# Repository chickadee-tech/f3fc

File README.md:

# Chickadee Tech F3FC #
This an STM32F3-based flight control Polystack board for multirotors designed by Chickadee Tech. It features an STM32F303VCT6 microcontroller and an MPU-6000 accelerometer/gyroscope. It runs a modified version of [Betaflight]() available [here](github.com/chickadee-tech/betaflight) with the CKD_F3FC target.

## Documentation ##
See the [wiki](https://github.com/chickadee-tech/f3fc/wiki) for documentation.

## Polystack ##
This **control** board is part of the Polystack platform for modular microcontrol systems. More information on the platform can be found at [polystack.org](http://polystack.org).

## Support ##
If you need support with a board you own or have development questions please email support@chickadee.tech or check chickadee.tech/support for other ways to get support.

## Support ##
If you need support with a board you own or have development questions please email support@chickadee.tech or check [chickadee.tech/support](https://chickadee.tech/support) for other ways to get support.

## Contributing ##
Please note that this project is released with a [Contributor Code of Conduct](CODE_OF_CONDUCT.md). By participating in this project you agree to abide by its terms.

### Setup ###
Components and footprints for PCB parts are not included in this repository. Instead, checkout the [chickadee-tech/kicad-libs](https://github.com/chickadee-tech/kicad-libs) repository in the same directory that this repository is checked out in. All part definitions should be relative so that they will load correctly.

### Pull requests ###
For fixes please submit a pull request to the original repository. After the pull request is merged, check the [Chickadee Tech Active Contributor Discount (ACD)](https://chickadee.tech/active-contributor) to see if you are eligible for a discount code to use on your next purchase.

### Derivatives ###
If developing your own version of the F3FC board please remove all Chickadee Tech trademarks and follow the [CC-BY license](LICENSE). While not required, please consider open sourcing your modifications so others can learn from your improvements. If you do email support@chickadee.tech and we may choose to add your project to the ACD.

You may also license the Polystack logo for free by emailing support@chickadee.tech. We'll ask for your gerbers to ensure the design complies with specifications laid out [here](https://github.com/chickadee-tech/polystack/wiki) and provide written permission to use the trademark after compliance has been demonstrated.

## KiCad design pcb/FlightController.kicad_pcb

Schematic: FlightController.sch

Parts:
C1: 2.2nF; C_0603_HandSoldering
C2, C3, C7, C8, C9, C10, C13: 0.1uF; C_0603_HandSoldering
C5: 10nF; C_0603_HandSoldering
C14: 2.2uF; C_0603_HandSoldering
D1: Green; LED-0603
D2: Yellow; LED-0603
D3: Red; LED-0603
P2: USB_OTG; Mini-USB-B
P3: CONN_02X04; Pin_Header_Angled_2x04
P4: CKD_SANDWICH; DF40-3-4mm-80pin-Receptacle
P10: SWDIO; Measurement_Point_Round-SMD-Pad_Small
P11: SWCLK; Measurement_Point_Round-SMD-Pad_Small
R1, R2, R3: 1k; R_0603_HandSoldering
R4, R11: 4.7k; R_0603_HandSoldering
R5: 10k+; R_0603_HandSoldering
R6: 1.5k; R_0603_HandSoldering
U1: MPU-6000; QFN-24-1EP_4x4mm_Pitch0.5mm
U2: STM32F303x{B,C}; LQFP-100_14x14mm_Pitch0.5mm
X1: 8MHZ; CSTCE_G-CSTCE_G_Z

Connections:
+5V: P4.19 (5V_0.3A), P4.20 (5V_0.3A), P4.21 (5V_0.3A), P4.22 (5V_0.3A), P4.23 (5V_0.3A), P4.24 (5V_0.3A); also elsewhere on the board
+5VA: P2.1 (VCC); also elsewhere on the board
+BATT: P4.18 (+BATT), U2.15 (PC0/ADC12_IN6); also elsewhere on the board
/ADC1: P4.49 (ADC1), U2.16 (PC1/ADC12_IN7)
/ADC2: P4.50 (ADC2), U2.17 (PC2/ADC12_IN8)
/GPIO2_4: P4.7 (GPIO3), U2.3 (PE4/TIM3_CH3)
/GPIO3_3: P4.8 (GPIO4), U2.2 (PE3/TIM3_CH2)
/GPIO4_2: P4.9 (xi2c_SDA), U2.1 (PE2/TIM3_CH1)
/LED0: R3.1, U2.7 (PC13)
/LED1: R2.1, U2.8 (PC14/OSC32_IN)
/LED2: R1.1, U2.9 (PC15/OSC32_OUT)
/MPU_INT: U1.12, U2.35 (PB0)
/PA14_SWCLK: P4.6 (GPIO2), P11.1, U2.76 (PA14/TIM8_CH2)
/PB7: P4.10 (xi2c_SCL), U2.93 (PB7/I2C1_SDA)
/Power/CURRENT: U2.18 (PC3/ADC12_IN9); also elsewhere on the board
/Reset/BOOT0: P4.65 (SPI4_NSS), R5.2, U2.94 (BOOT0); also elsewhere on the board
/Reset/RESET: C13.1, P4.66 (SPI4_SCK), U2.14 (NRST); also elsewhere on the board
/SPI1_MISO: U1.9, U2.31 (PA6/SPI1_MISO)
/SPI1_MOSI: U1.24, U2.32 (PA7/SPI1_MOSI)
/SPI1_NSS: U1.8, U2.29 (PA4/SPI1_NSS)
/SPI1_SCK: U1.23, U2.30 (PA5/SPI1_SCK)
/SPI2_MISO: P4.79 (SPI1_MISO), U2.53 (PB14/SPI2_MISO)
/SPI2_MOSI: P4.80 (SPI1_MOSI), U2.54 (PB15/SPI2_MOSI)
/SPI2_NSS: P4.77 (SPI1_NSS), U2.51 (PB12/SPI2_NSS)
/SPI2_SCK: P4.78 (SPI1_SCK), U2.52 (PB13/SPI2_SCK)
/SPI3_MISO: P4.75 (SPI2_MISO), U2.90 (PB4/SPI3_MISO)
/SPI3_MOSI: P4.76 (SPI2_MOSI), U2.91 (PB5/SPI3_MOSI)
/SPI3_NSS: P4.73 (SPI2_NSS), U2.77 (PA15/SPI3_NSS)
/SPI3_SCK: P4.74 (SPI2_SCK), U2.89 (PB3/SPI3_SCK)
/SWDIO_13: P4.5 (GPIO1), P10.1, U2.72 (PA13)
/TIM1_CH1: P3.2, U2.40 (PE9/TIM1_CH1)
/TIM1_CH2: P3.4, U2.42 (PE11/TIM1_CH2)
/TIM1_CH3: P3.6, U2.44 (PE13/TIM1_CH3)
/TIM1_CH4: P3.8, U2.45 (PE14/TIM1_CH4)
/TIM2_CH3: P4.3 (TIM3), P4.27 (UART7_TX), U2.47 (PB10/TIM2_CH3)
/TIM2_CH4: P4.28 (UART7_RX), U2.48 (PB11/TIM2_CH4)
/TIM15_CH1: P4.4 (TIM4), P4.29 (UART6_TX), U2.25 (PA3/TIM15_CH1)
/TIM15_CH2: P4.30 (UART6_RX), U2.26 (PA3/TIM15_CH2)
/TIM16_CH1: P4.1 (TIM1), U2.95 (PB8/TIM16_CH1)
/TIM17_CH1: P4.2 (TIM2), U2.96 (PB9/TIM17_CH1)
/TIMG1_CH1: P4.41 (TIMG1_CH1), U2.66 (PC9/TIM3_CH4)
/TIMG1_CH2: P4.42 (TIMG1_CH2), U2.65 (PC8/TIM3_CH3)
/TIMG1_CH3: P4.43 (TIMG1_CH3), U2.64 (PC7/TIM3_CH2)
/TIMG1_CH4: P4.44 (TIMG1_CH4), U2.63 (PC6/TIM3_CH1)
/TIMG2_CH1: P4.45 (TIMG2_CH1), U2.62 (PD15/TIM4_CH4)
/TIMG2_CH2: P4.46 (TIMG2_CH2), U2.61 (PD14/TIM4_CH3)
/TIMG2_CH3: P4.47 (TIMG2_CH3), U2.60 (PD13/TIM4_CH2)
/TIMG2_CH4: P4.48 (TIMG2_CH4), U2.59 (PD12/TIM4_CH1)
/UART1_RX: P4.36 (UART3_RX), U2.98 (PE1/USART1_RX)
/UART1_TX: P4.35 (UART3_TX), U2.97 (PE0/USART1_TX)
/UART2_RX: P4.38 (UART2_RX), U2.87 (PD6/USART2_RX)
/UART2_TX: P4.37 (UART2_TX), U2.86 (PD5/USART2_TX)
/UART3_RX: P4.40 (UART1_RX), U2.56 (PD9/USART3_RX)
/UART3_TX: P4.39 (UART1_TX), U2.55 (PD8/USART3_TX)
/UART4_RX: P4.34 (UART4_RX), U2.79 (PC11/UART4_RX)
/UART4_TX: P4.33 (UART4_TX), U2.78 (PC10/UART4_TX)
/UART5_RX: P4.32 (UART5_RX), U2.83 (PD2/UART5_RX)
/UART5_TX: P4.31 (UART5_TX), U2.80 (PC12/UART5_TX)
/USB_D+: P2.3 (D+), R6.1, U2.71 (PA12/USB_DP)
/USB_D-: P2.2 (D-), U2.70 (PA11/USB_DM)
/si2c_SCL: P4.12 (si2c_SCL), R11.2, U2.68 (PA9/I2C2_SCL)
/si2c_SDA: P4.11 (si2c_SDA), R4.2, U2.69 (PA10/I2C2_SDA)
GNDPWR: C1.1, C2.2, C3.2, C5.1, C7.1, C8.2, C9.2, C10.2, C13.2, C14.1, P2.5 (GND), P2.6 (shield), P3.1, P3.3, P3.5, P3.7, P4.13 (HEIGHT_4), P4.14 (HEIGHT_2), P4.57 (GND), P4.58 (GND), P4.59 (GND), P4.60 (GND), P4.61 (GND), P4.62 (GND), P4.63 (GND), P4.64 (GND), R5.1, U1.11, U1.18, U2.20 (VSSA/VREF-), U2.49 (VSS_2), U2.74 (VSS_3), U2.99 (VSS_1), X1.3; also elsewhere on the board
unnamed: C1.2, U1.20
unnamed: C2.1, U1.10
unnamed: D1.1 (K), R1.2
unnamed: D2.1 (K), R2.2
unnamed: D3.1 (K), R3.2
unnamed: U2.12 (PF0/OSC_IN), X1.1
unnamed: U2.13 (PF1/OSC_OUT), X1.2
VDD: C3.1, C5.2, C7.2, C8.1, C9.1, C10.1, C14.2, D1.2 (A), D2.2 (A), D3.2 (A), P4.15 (HEIGHT_1), P4.16 (3V3_0.3A_LL), R4.1, R6.2, R11.1, U1.13, U2.6 (VBAT), U2.21 (VREF+), U2.22 (VDDA), U2.28 (VDD_4), U2.50 (VDD_2), U2.75 (VDD_3), U2.100 (VDD_1); also elsewhere on the board

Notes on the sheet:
Chickadee Tech F3FC v9
Copyright 2016 Chickadee Tech LLC, <add attributions here> This work is licensed under the Creative Commons Attribution 4.0 International License. To view a copy of this license, visit http://creativecommons.org/licenses/by/4.0/ or send a letter to Creative Commons, PO Box 1866, Mountain View, CA 9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

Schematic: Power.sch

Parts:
C11: 10uF+; C_1206_HandSoldering
C12: 1uF+; C_0603_HandSoldering
D4: D_Schottky_x2_KCom_AAK; SOT-23
D5: Red; LED-0603
P1: 3V3; Measurement_Point_Round-SMD-Pad_Small
P5: CONN_02X10; DF40-20pin-Header
P8: CONN_01X01; Measurement_Point_Square-SMD-Pad_Small
P9: 5V; Measurement_Point_Round-SMD-Pad_Small
R12: 1k; R_0603_HandSoldering
U3: TLV70233DBV; SOT-23-5

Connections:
+5V: D4.1, P5.3, P5.5, P5.7, P5.9, P5.11, P5.13, P5.15, P5.17; also elsewhere on the board
+5VA: D4.2; also elsewhere on the board
+BATT: P5.19; also elsewhere on the board
/Power/CURRENT: P5.1; also elsewhere on the board
GNDPWR: C11.2, C12.2, P5.2, P5.4, P5.6, P5.8, P5.10, P5.12, P5.14, P5.16, P5.18, P5.20, P8.1, R12.2, U3.2 (GND); also elsewhere on the board
unnamed: C11.1, D4.3, P9.1, U3.1 (IN), U3.3 (EN)
unnamed: D5.1 (K), R12.1
VDD: C12.1, D5.2 (A), P1.1, U3.5 (OUT); also elsewhere on the board

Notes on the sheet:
USB Power
Copyright 2016 Chickadee Tech LLC, <add attributions here> This work is licensed under the Creative Commons Attribution 4.0 International License. To view a copy of this license, visit http://creativecommons.org/licenses/by/4.0/ or send a letter to Creative Commons, PO Box 1866, Mountain View, CA 9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

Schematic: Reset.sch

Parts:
C15: 2.2uF; C_0603_HandSoldering
P6: RESET; Measurement_Point_Round-SMD-Pad_Small
P7: BOOT0; Measurement_Point_Round-SMD-Pad_Small
Q1: Q_PMOS_GSD; SOT-23
Q3, Q4: Q_NMOS_GSD; SOT-23
R7: 10k; R_0603_HandSoldering
R9: 470k; R_0603_HandSoldering
R10: 100k; R_0603_HandSoldering
SW1: SW_PUSH; SW_SPST_EVQP7A

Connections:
/Reset/BOOT0: P7.1, Q1.3; also elsewhere on the board
/Reset/RESET: P6.1, Q3.1, SW1.2; also elsewhere on the board
GNDPWR: C15.2, Q3.2, Q4.2, SW1.1; also elsewhere on the board
unnamed: C15.1, Q4.1, R10.1
unnamed: Q1.1, Q4.3, R7.2
unnamed: Q3.3, R9.2, R10.2
VDD: Q1.2, R7.1, R9.1; also elsewhere on the board

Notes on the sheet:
Internally Pulled High
Pulled Low
Copyright 2016 Chickadee Tech LLC, <add attributions here> This work is licensed under the Creative Commons Attribution 4.0 International License. To view a copy of this license, visit http://creativecommons.org/licenses/by/4.0/ or send a letter to Creative Commons, PO Box 1866, Mountain View, CA 9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

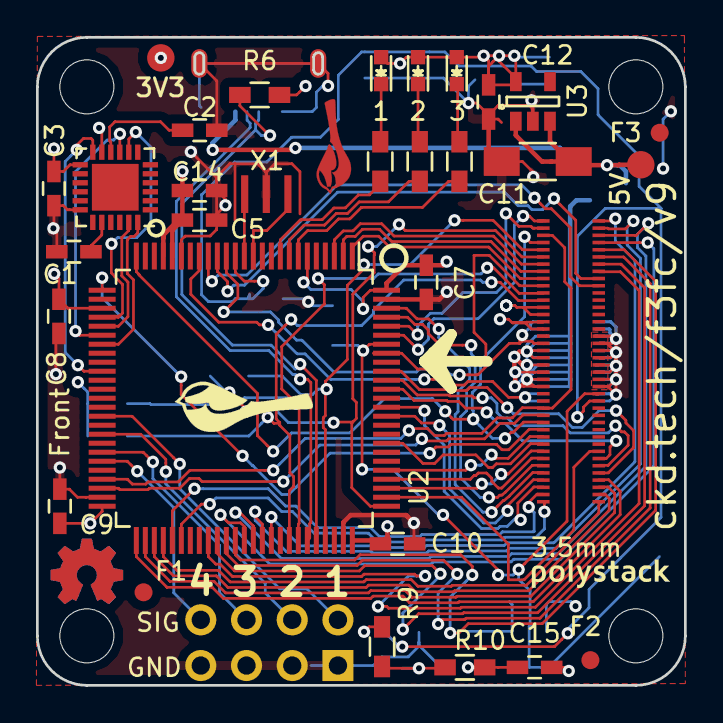
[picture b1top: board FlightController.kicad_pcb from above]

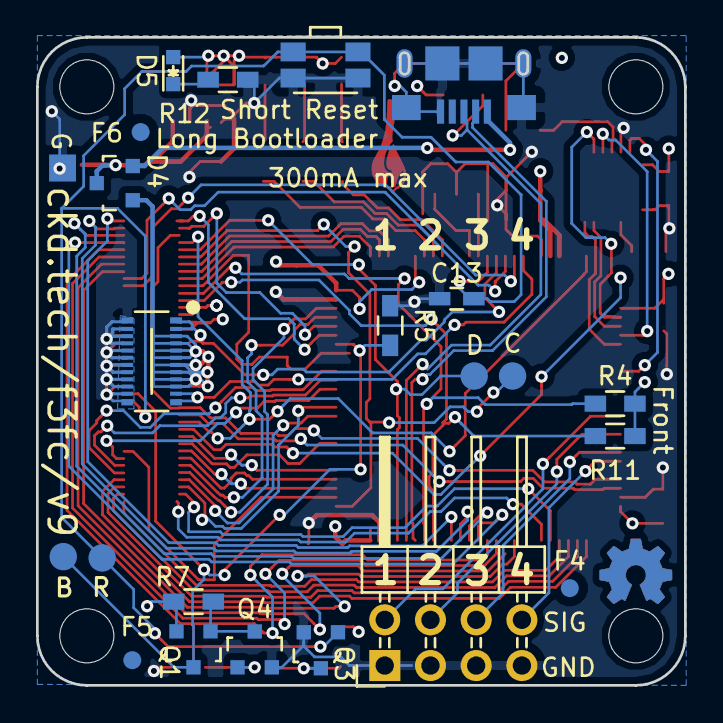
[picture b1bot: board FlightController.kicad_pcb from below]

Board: 4 copper layers, 36.0 x 36.0 mm, 55 parts (23 on the bottom side), 76 nets.

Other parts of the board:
F1, F2, F3, F4, F5, F6: 1mm; Fiducial
svg2mod: G***; polystack-bold-0.4

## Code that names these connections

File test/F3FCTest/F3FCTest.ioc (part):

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Mcu.Name=STM32F303V(B-C)Tx
Mcu.Package=LQFP100
Mcu.UserName=STM32F303VCTx
PA11.Mode=Device
PA11.Signal=USB_DM
PA12.Mode=Device
PA12.Signal=USB_DP
PA13.Mode=Serial-Wire
PA13.Signal=SYS_JTMS-SWDIO
PA14.Mode=Serial-Wire
PA14.Signal=SYS_JTCK-SWCLK
PA2.Mode=Asynchronous
PA2.Signal=USART2_TX
PA3.Mode=Asynchronous
PA3.Signal=USART2_RX
PB10.Mode=Asynchronous
PB10.Signal=USART3_TX
PC10.Mode=Asynchronous
PC10.Signal=UART4_TX
PC11.Mode=Asynchronous
PC11.Signal=UART4_RX
PC12.Mode=Asynchronous
PC12.Signal=UART5_TX
PC13.Signal=GPIO_Output
PC14-OSC32_IN.Signal=GPIO_Output
PC15-OSC32_OUT.Signal=GPIO_Output
PD2.Mode=Asynchronous
PD2.Signal=UART5_RX
PE15.Mode=Asynchronous
PE15.Signal=USART3_RX
PF0-OSC_IN.Mode=HSE-External-Oscillator
PF0-OSC_IN.Signal=RCC_OSC_IN
PF1-OSC_OUT.Mode=HSE-External-Oscillator
PF1-OSC_OUT.Signal=RCC_OSC_OUT
RCC.HSEPLLFreq_Value=8000000
RCC.HSE_VALUE=8000000
RCC.SYSCLKFreq_VALUE=72000000
RCC.SYSCLKSourceVirtual=RCC_SYSCLKSOURCE_PLLCLK
board=F3FCTest

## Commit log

2015-11-08 v1 of the f3 flight controller
2015-11-08 Consolidate gitignore
2015-11-08 Shuffle around libraries so they are more easily shared.
2015-11-10 v1 of f3fc
2015-11-10 v2 of the f3fc which adds pull up resistors for the i2c lines.
2015-11-25 v3 of f3fc. Correct mosfet pinout. Add measurement points. Remove MPU. Tweaked pinout with one less SPI.
2015-12-18 Initial blinky for f3fc. Compiles but not tested on the board.
2016-01-07 Move decoupling caps to the front side of the board, re-add the MPU and switch from a crystal to a resonator.
2016-01-11 v4 of F3FC including stacking height label
2016-02-02 v5 of F3FC. Adjusts motor output location, switches to MPU-6000 and adds chickadee logo back.
2016-03-05 F3FC v6 which features correct reset circuitry.
    Also:
    * Routes USB as differential pair.
    * Corrects reset circuit.
    * Adds fiducials
    * Matches up LED numbering to reference
    * Supports current pin from power connector.
2016-03-23 Remove g2l and g3l layers. OSH Park support g2 and g3 now.
2016-04-07 More changes to F3. Can't remember what.
2016-04-13 Rebrand everything to Polystack and increment versions.
2016-04-16 Final gerbers for test manufacturing run.
2016-06-07 Update polystack logo to bold variant and bump version number.
2016-07-07 Add license information to many files. PCB design files are CC-BY and code is MIT license.
2016-07-07 Add back .gitignore after repo split.
2016-07-07 Convert to relative component and footprint paths.

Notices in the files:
pcb/FlightController.kicad_pcb:
or send a letter to Creative Commons, PO Box 1866, Mountain View, CA 94042, USA.
